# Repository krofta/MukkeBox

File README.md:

# MukkeBox_Electric

This is a project made with KiCAD.
During corona virus i was pretty bored at home and started to build my own portable bluetooth speaker and this is the result.
Additional I have to more repositories for software and mechanics:  
https://github.com/krofta/MukkeBox_Mechanic  
https://github.com/krofta/MukkeBox_Software

This PCB contains:  
Charger for 1-6s LiPo Packs (configured for 4s)  TI BQ24610  
ST microcontroller to controll the whole circuit STM32F030C6Tx  
Step up to make 4s pack-voltage to constant 24V TI TPS40210
Digital audio processor ST TDA7719 with i2c interface  
2x Class D audio amplifiers TI TPA3116D2  (in 2.1 sound system configuration with 20dB gain)

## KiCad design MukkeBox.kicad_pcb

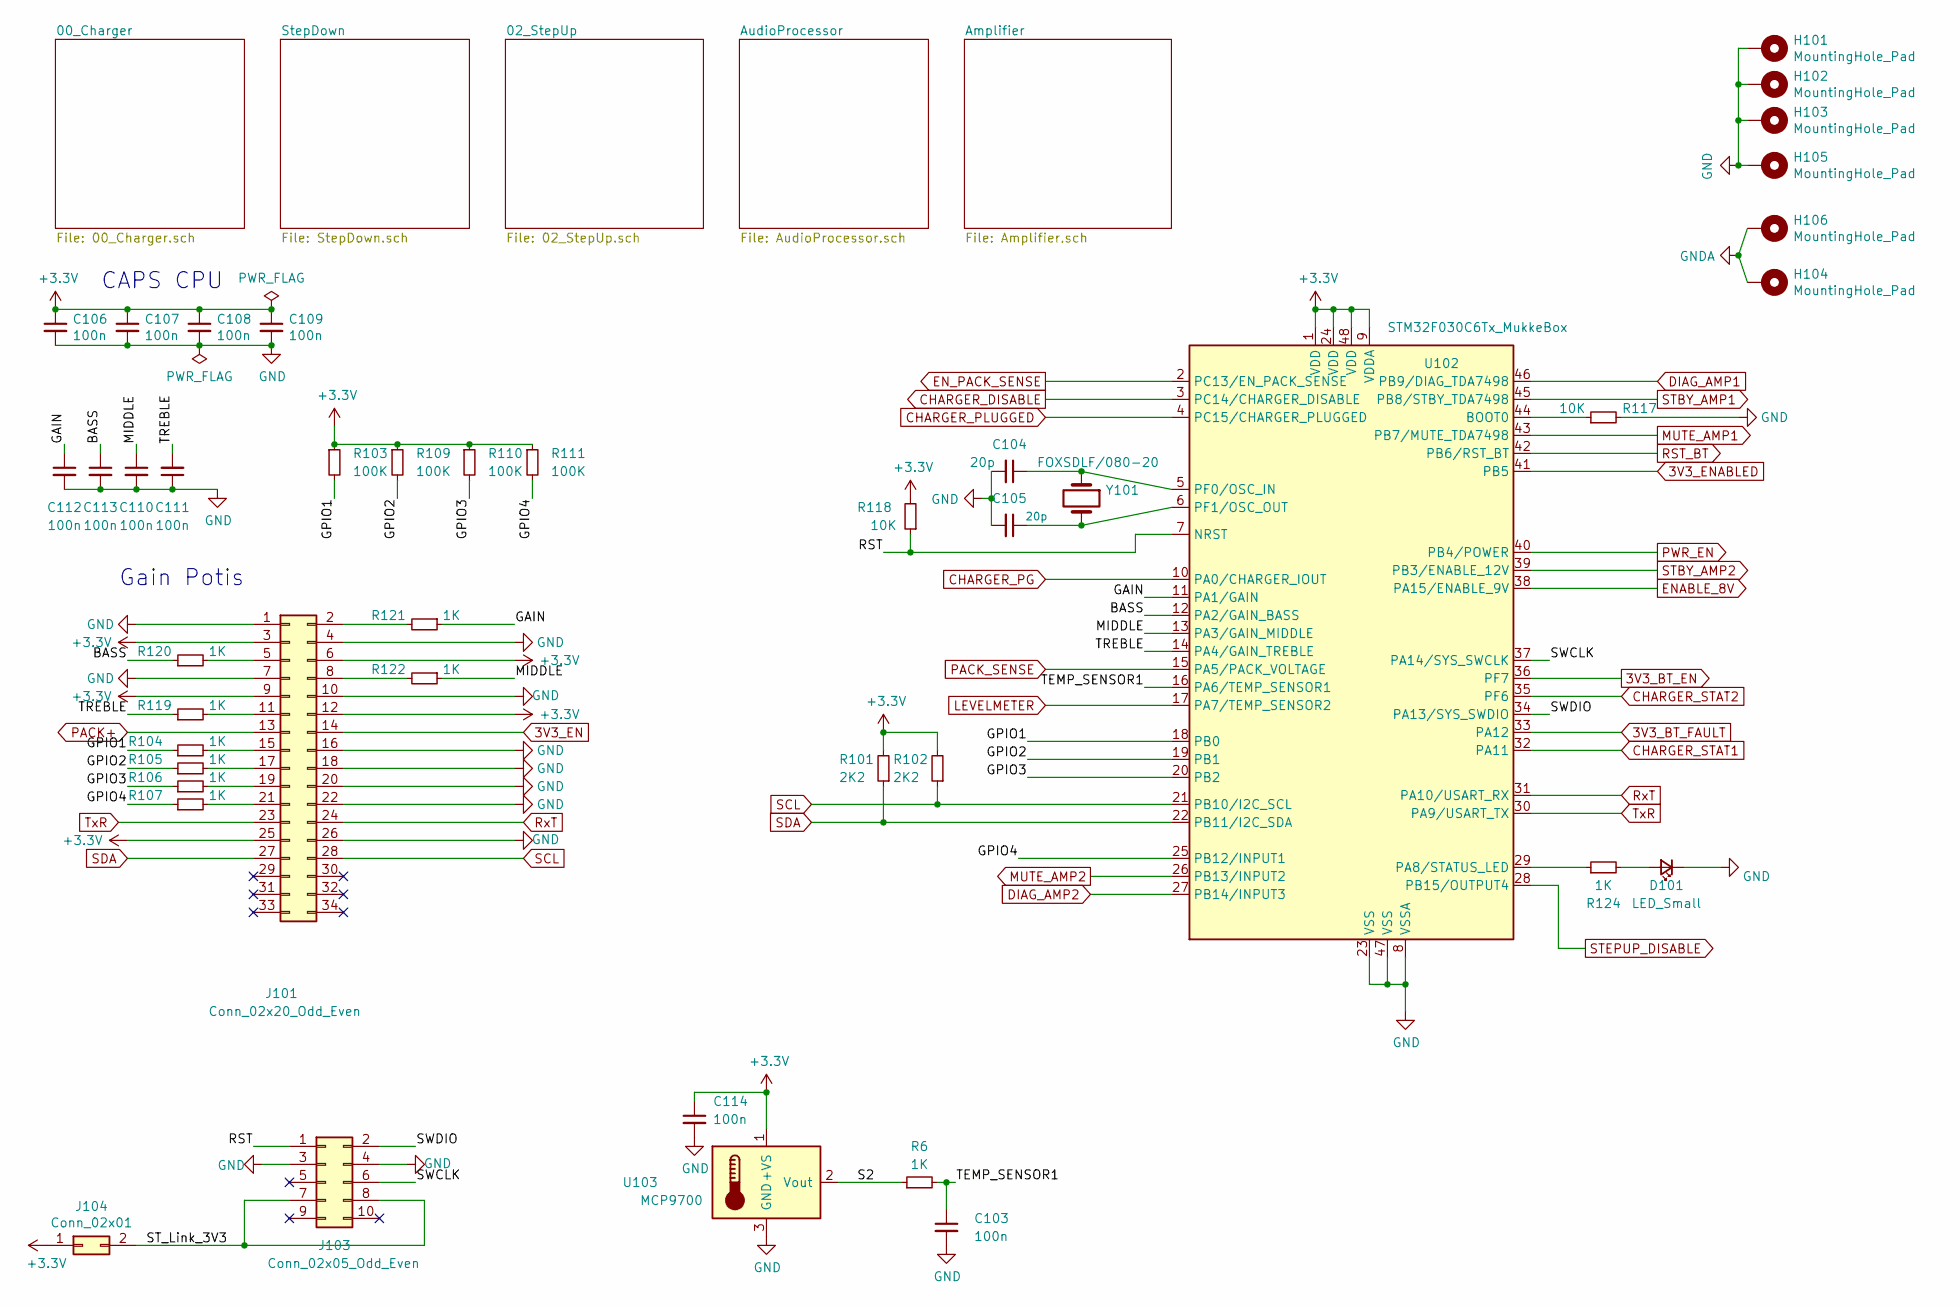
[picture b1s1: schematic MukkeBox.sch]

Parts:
C103, C106, C107, C108, C109, C110, C111, C112, C113, C114: 100n; C_0603_1608Metric_Pad1.05x0.95mm_HandSolder
C104, C105: 20p; C_0603_1608Metric_Pad1.05x0.95mm_HandSolder
D101: LED_Small; LED_D3.0mm
H101, H102, H103, H104, H105, H106: MountingHole_Pad; MountingHole_3.2mm_M3_DIN965_Pad
J101: Conn_02x20_Odd_Even; PinHeader_2x17_P2.54mm_Vertical
J103: Conn_02x05_Odd_Even; PinHeader_2x05_P2.54mm_Vertical
J104: Conn_02x01; PinHeader_1x02_P2.54mm_Vertical
R6, R104, R105, R106, R107, R119, R120, R121, R122, R124: 1K; R_0603_1608Metric_Pad1.05x0.95mm_HandSolder
R101, R102: 2K2; R_0603_1608Metric_Pad1.05x0.95mm_HandSolder
R103, R109, R110, R111: 100K; R_0603_1608Metric_Pad1.05x0.95mm_HandSolder
R117, R118: 10K; R_0603_1608Metric_Pad1.05x0.95mm_HandSolder
U102: STM32F030C6Tx_MukkeBox; LQFP-48_7x7mm_P0.5mm
U103: MCP9700; TO-92_Inline
Y101: FOXSDLF/080-20; Crystal_SMD_HC49-SD

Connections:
3V3_BT_EN: U102.36 (PF7); also elsewhere on the board
3V3_BT_FAULT: U102.33 (PA12); also elsewhere on the board
3V3_EN: J101.14; also elsewhere on the board
3V3_ENABLED: U102.41 (PB5); also elsewhere on the board
/BASS: C113.1, R120.1, U102.12 (PA2/GAIN_BASS)
/GAIN: C112.1, R121.1, U102.11 (PA1/GAIN)
/GPIO1: R103.2, R104.1, U102.18 (PB0)
/GPIO2: R105.1, R109.2, U102.19 (PB1)
/GPIO3: R106.1, R110.2, U102.20 (PB2)
/GPIO4: R107.1, R111.2, U102.25 (PB12/INPUT1)
/MIDDLE: C110.1, R122.1, U102.13 (PA3/GAIN_MIDDLE)
/RST: J103.1, R118.1, U102.7 (NRST)
/S2: R6.1, U103.2 (Vout)
/ST_Link_3V3: J103.7, J103.8, J104.2
/SWCLK: J103.6, U102.37 (PA14/SYS_SWCLK)
/SWDIO: J103.2, U102.34 (PA13/SYS_SWDIO)
/TEMP_SENSOR1: C103.1, R6.2, U102.16 (PA6/TEMP_SENSOR1)
/TREBLE: C111.2, R119.1, U102.14 (PA4/GAIN_TREBLE)
CHARGER_DISABLE: U102.3 (PC14/CHARGER_DISABLE); also elsewhere on the board
CHARGER_PG: U102.10 (PA0/CHARGER_IOUT); also elsewhere on the board
CHARGER_PLUGGED: U102.4 (PC15/CHARGER_PLUGGED); also elsewhere on the board
CHARGER_STAT1: U102.32 (PA11); also elsewhere on the board
CHARGER_STAT2: U102.35 (PF6); also elsewhere on the board
DIAG_AMP1: U102.46 (PB9/DIAG_TDA7498); also elsewhere on the board
DIAG_AMP2: U102.27 (PB14/INPUT3); also elsewhere on the board
ENABLE_8V: U102.38 (PA15/ENABLE_9V); also elsewhere on the board
EN_PACK_SENSE: U102.2 (PC13/EN_PACK_SENSE); also elsewhere on the board
GND: C103.2, C104.2, C105.2, C106.2, C107.2, C108.2, C109.2, C110.2, C111.1, C112.2, C113.2, C114.2, D101.1 (K), H101.1, H102.1, H103.1, H105.1, J101.1, J101.4, J101.7, J101.10, J101.16, J101.18, J101.20, J101.22, J101.26, J103.3, J103.4, R117.2, U102.8 (VSSA), U102.23 (VSS), U102.47 (VSS), U103.3 (GND); also elsewhere on the board
GNDA: H104.1, H106.1; also elsewhere on the board
LEVELMETER: U102.17 (PA7/TEMP_SENSOR2); also elsewhere on the board
MUTE_AMP1: U102.43 (PB7/MUTE_TDA7498); also elsewhere on the board
MUTE_AMP2: U102.26 (PB13/INPUT2); also elsewhere on the board
unnamed: C104.1, U102.5 (PF0/OSC_IN), Y101.1
unnamed: C105.1, U102.6 (PF1/OSC_OUT), Y101.2
unnamed: D101.2 (A), R124.2
unnamed: J101.2, R121.2
unnamed: J101.5, R120.2
unnamed: J101.8, R122.2
unnamed: J101.11, R119.2
unnamed: J101.15, R104.2
unnamed: J101.17, R105.2
unnamed: J101.19, R106.2
unnamed: J101.21, R107.2
unnamed: R117.1, U102.44 (BOOT0)
unnamed: R124.1, U102.29 (PA8/STATUS_LED)
PACK+: J101.13; also elsewhere on the board
PACK_SENSE: U102.15 (PA5/PACK_VOLTAGE); also elsewhere on the board
PWR_EN: U102.40 (PB4/POWER); also elsewhere on the board
RST_BT: U102.42 (PB6/RST_BT); also elsewhere on the board
RxT: J101.24, U102.31 (PA10/USART_RX); also elsewhere on the board
SCL: J101.28, R102.1, U102.21 (PB10/I2C_SCL); also elsewhere on the board
SDA: J101.27, R101.1, U102.22 (PB11/I2C_SDA); also elsewhere on the board
STBY_AMP1: U102.45 (PB8/STBY_TDA7498); also elsewhere on the board
STBY_AMP2: U102.39 (PB3/ENABLE_12V); also elsewhere on the board
STEPUP_DISABLE: U102.28 (PB15/OUTPUT4); also elsewhere on the board
TxR: J101.23, U102.30 (PA9/USART_TX); also elsewhere on the board

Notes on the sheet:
Gain Potis
CAPS CPU

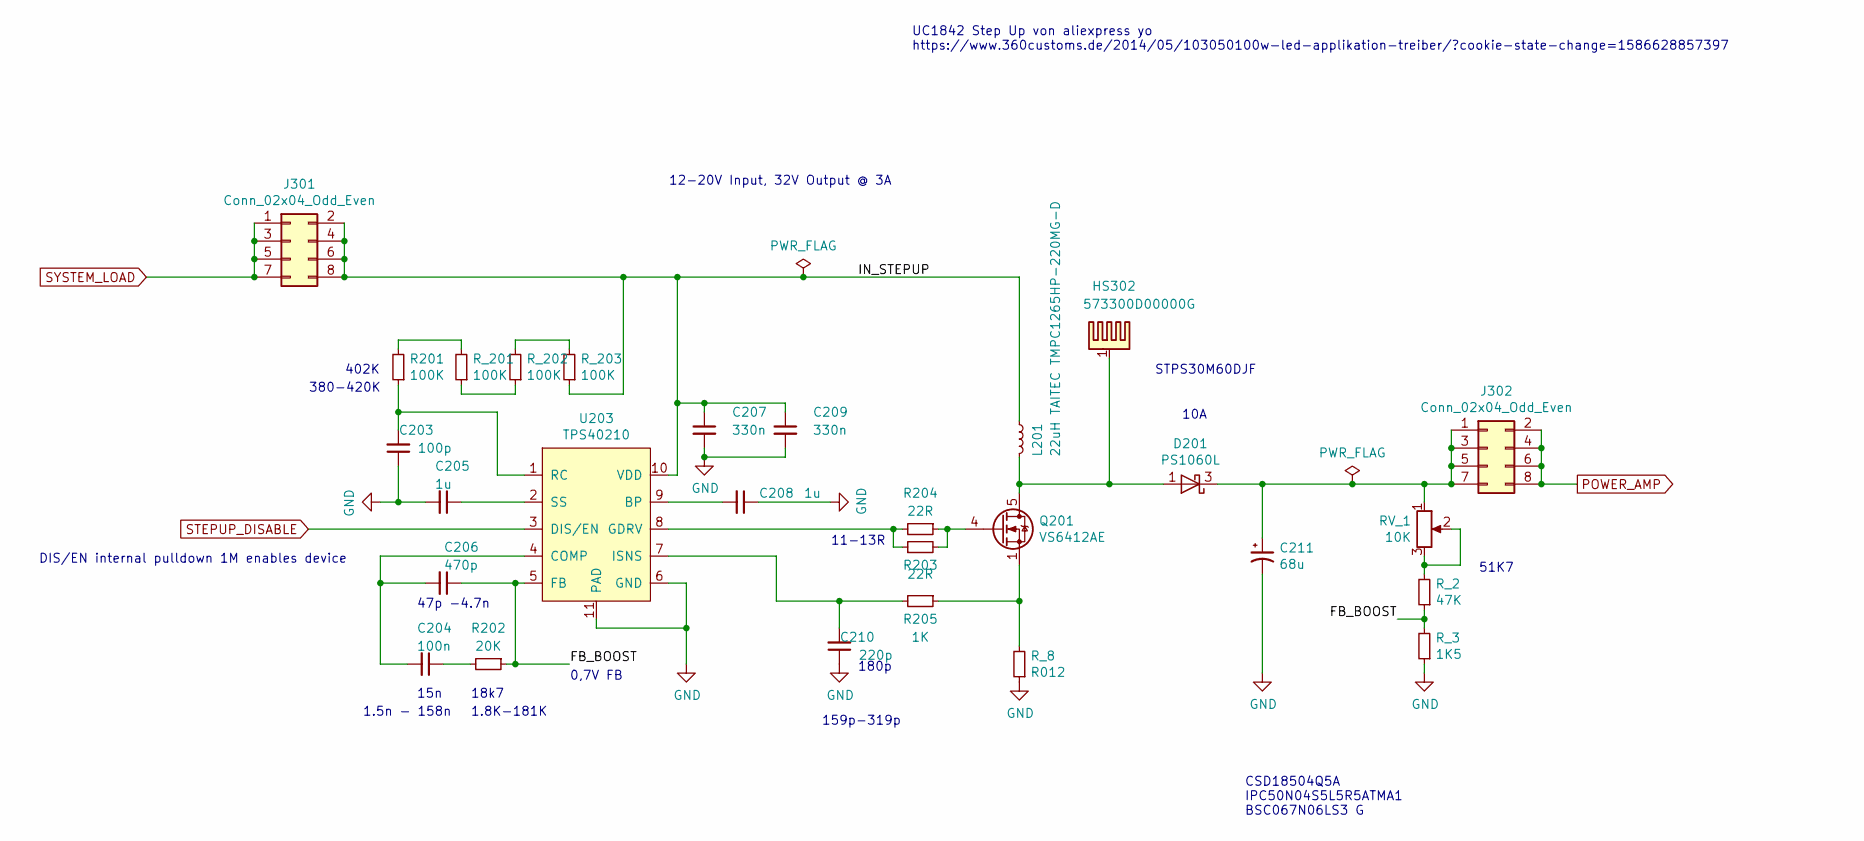
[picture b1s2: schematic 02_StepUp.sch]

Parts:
C203: 100p; C_0603_1608Metric_Pad1.05x0.95mm_HandSolder
C204: 100n; C_0603_1608Metric_Pad1.05x0.95mm_HandSolder
C205, C208: 1u; C_0603_1608Metric_Pad1.05x0.95mm_HandSolder
C206: 470p; C_0603_1608Metric_Pad1.05x0.95mm_HandSolder
C207, C209: 330n; C_1206_3216Metric
C210: 220p; C_0603_1608Metric_Pad1.05x0.95mm_HandSolder
C211: 68u; CP_Radial_D5.0mm_P2.50mm
D201: PS1060L; TO-277B
HS302: 573300D00000G; Heatsink_AAVID_573300D00010G_TO-263
J301, J302: Conn_02x04_Odd_Even; PinHeader_2x04_P2.54mm_Vertical
L201: 22uH TAITEC TMPC1265HP-220MG-D; TAITEC TMPC1265HP-220MG-D
Q201: VS6412AE; Diodes_PowerDI3333-8
R201: 100K; R_0603_1608Metric_Pad1.05x0.95mm_HandSolder
R202: 20K; R_0603_1608Metric_Pad1.05x0.95mm_HandSolder
R203, R204: 22R; R_0603_1608Metric_Pad1.05x0.95mm_HandSolder
R205: 1K; R_0603_1608Metric_Pad1.05x0.95mm_HandSolder
RV_1: 10K; Potentiometer_P250
R_2: 47K; R_0603_1608Metric_Pad1.05x0.95mm_HandSolder
R_3: 1K5; R_0603_1608Metric_Pad1.05x0.95mm_HandSolder
R_8: R012; R_2512_6332Metric_Pad1.52x3.35mm_HandSolder
R_201, R_202, R_203: 100K; R_0603_1608Metric_Pad1.05x0.95mm_HandSolder
U203: TPS40210; MSOP-10-1EP_3x3mm_P0.5mm_EP1.68x1.88mm

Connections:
/02_StepUp/FB_BOOST: C206.1, R202.1, R_2.1, R_3.2, U203.5 (FB); also elsewhere on the board
/02_StepUp/IN_STEPUP: C207.1, C209.1, J301.2, J301.4, J301.6, J301.8, L201.1, R_203.1, U203.10 (VDD); also elsewhere on the board
GND: C203.1, C205.2, C207.2, C208.1, C209.2, C210.1, C211.2, R_3.1, R_8.1, U203.6 (GND), U203.11 (PAD); also elsewhere on the board
unnamed: C203.2, R201.1, U203.1 (RC)
unnamed: C204.1, R202.2
unnamed: C204.2, C206.2, U203.4 (COMP)
unnamed: C205.1, U203.2 (SS)
unnamed: C208.2, U203.9 (BP)
unnamed: C210.2, R205.2, U203.7 (ISNS)
unnamed: C211.1, D201.3 (K), J302.1, J302.3, J302.5, J302.7, RV_1.1
unnamed: D201.1 (A), D201.2 (A), HS302.1, L201.2, Q201.5 (D)
unnamed 147: Q201.1 (S), Q201.2 (S), Q201.3 (S), R205.1, R_8.2; also elsewhere on the board
unnamed: Q201.4 (G), R203.2, R204.1
unnamed 167: R201.2, R_201.2; also elsewhere on the board
unnamed: R203.1, R204.2, U203.8 (GDRV)
unnamed 169: RV_1.2, RV_1.3, R_2.2; also elsewhere on the board
unnamed: R_201.1, R_202.1
unnamed: R_202.2, R_203.2
POWER_AMP: J302.2, J302.4, J302.6, J302.8; also elsewhere on the board
STEPUP_DISABLE: U203.3 (DIS/EN); also elsewhere on the board
SYSTEM_LOAD: J301.1, J301.3, J301.5, J301.7; also elsewhere on the board

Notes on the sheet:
UC1842 Step Up von aliexpress yo https://www.360customs.de/2014/05/103050100w-led-applikation-treiber/?cookie-state-change=1586628857397
DIS/EN internal pulldown 1M enables device
12-20V Input, 32V Output @ 3A
51K7
18k7
15n
402K
180p
10A
47p -4.7n
1.5n - 158n
1.8K-181K
159p-319p
11-13R
380-420K
CSD18504Q5A IPC50N04S5L5R5ATMA1 BSC067N06LS3 G
STPS30M60DJF
0,7V FB

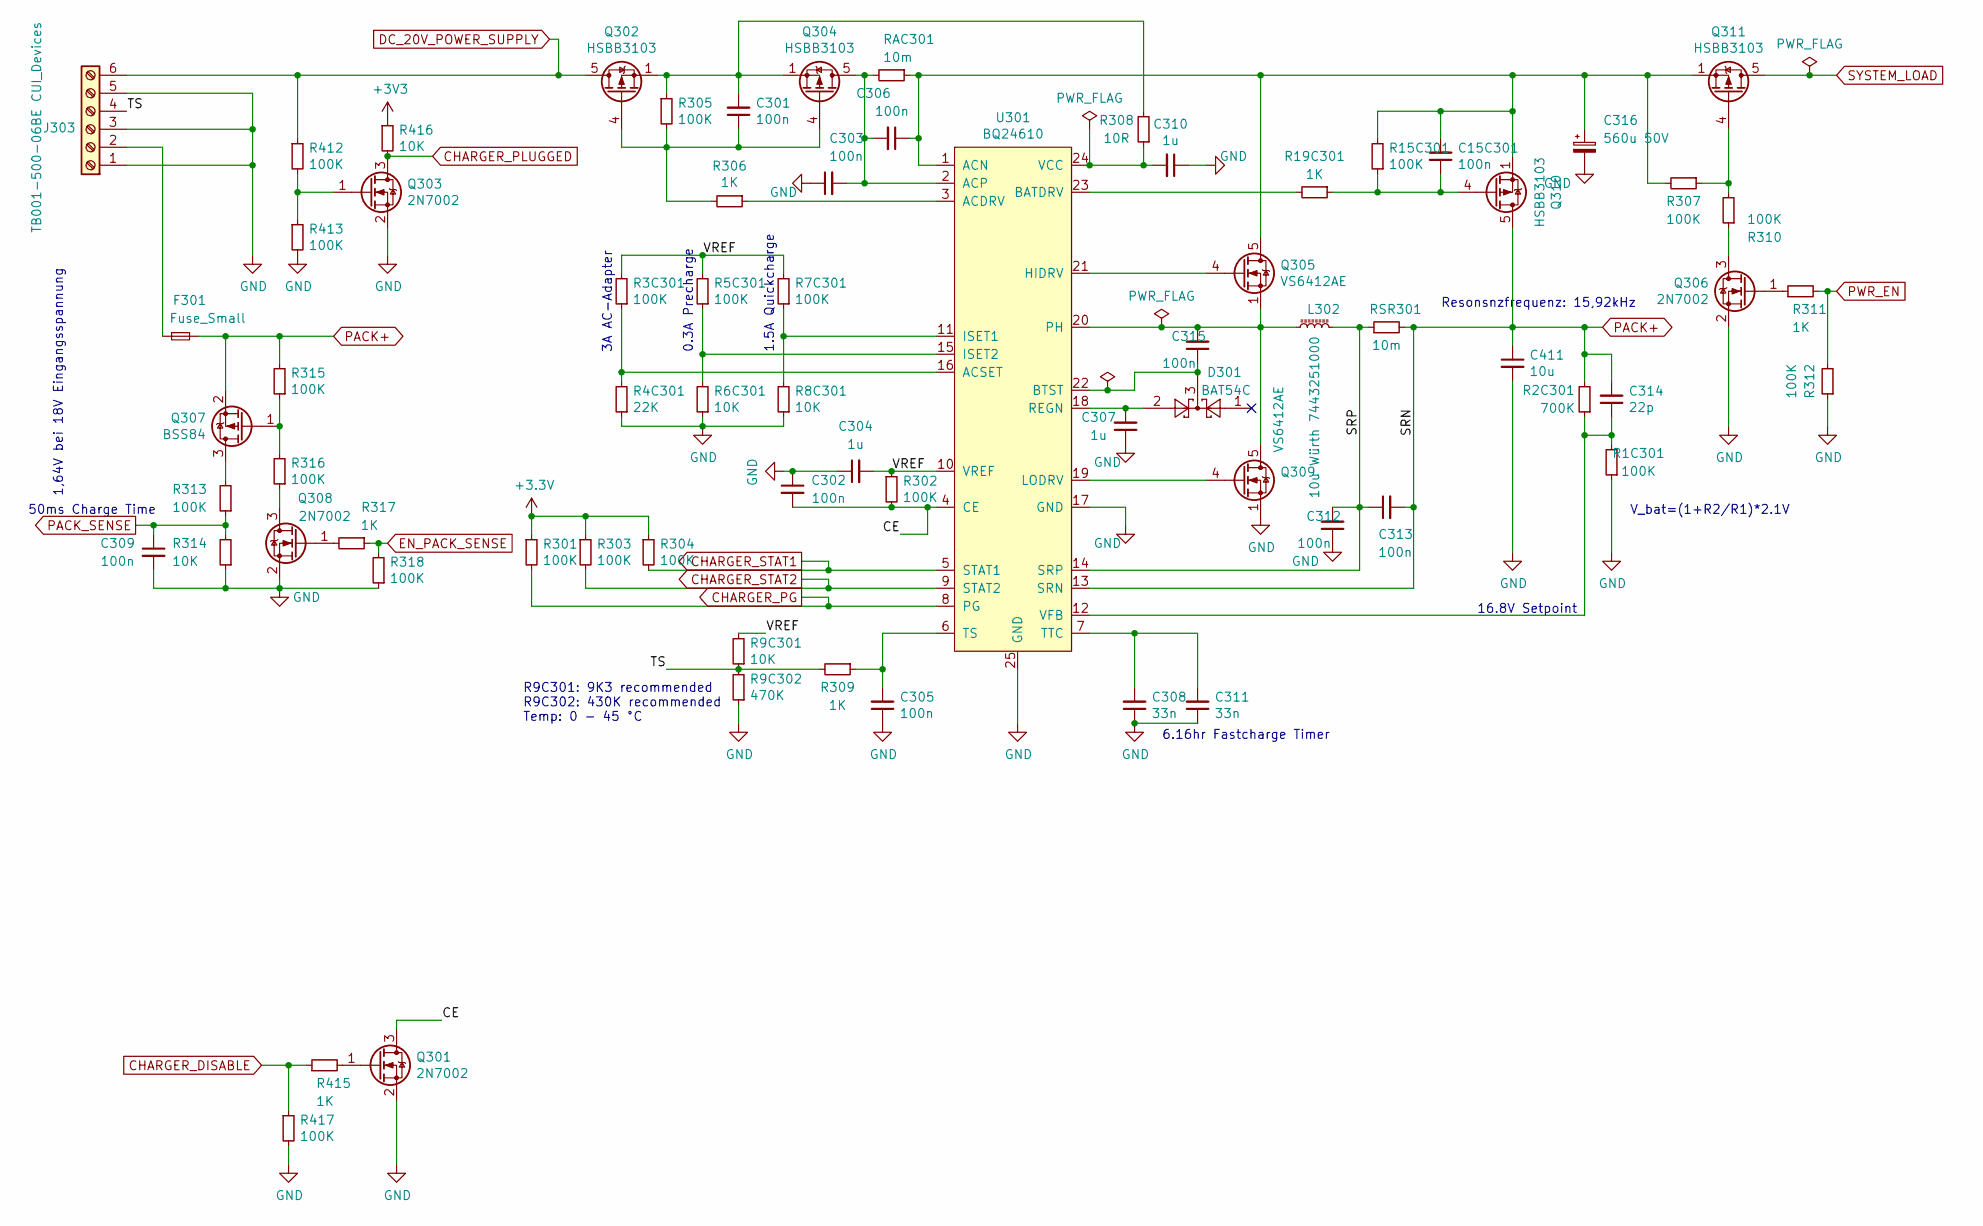
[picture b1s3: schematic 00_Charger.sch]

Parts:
C15C301, C301, C302, C303, C305, C306, C309, C312, C313, C315: 100n; C_0603_1608Metric_Pad1.05x0.95mm_HandSolder
C304, C307, C310: 1u; C_1210_3225Metric
C308, C311: 33n; C_0603_1608Metric_Pad1.05x0.95mm_HandSolder
C314: 22p; C_0603_1608Metric_Pad1.05x0.95mm_HandSolder
C316: 560u 50V; CP_Radial_D12.5mm_P5.00mm
C411: 10u; C_1206_3216Metric_Pad1.42x1.75mm_HandSolder
D301: BAT54C; SOT-23
F301: Fuse_Small; Fuseholder_Cylinder-5x20mm_Schurter_0031_8201_Horizontal_Op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
J303: TB001-500-06BE CUI_Devices; TerminalBlock_RND_205-00049_1x06_P5.00mm_Horizontal
L302: 10u Würth 7443251000; L_Wuerth_HCI-1050
Q301, Q303, Q306, Q308: 2N7002; SOT-23
Q302, Q304, Q310, Q311: HSBB3103; Diodes_PowerDI3333-8
Q305, Q309: VS6412AE; Diodes_PowerDI3333-8
Q307: BSS84; SOT-23
R1C301, R3C301, R5C301, R7C301, R15C301, R301, R302, R303, R304, R305, R307, R310, R312, R313, R315, R316, R318, R412, R413, R417: 100K; R_0603_1608Metric_Pad1.05x0.95mm_HandSolder
R2C301: 700K; R_0603_1608Metric_Pad1.05x0.95mm_HandSolder
R4C301: 22K; R_0603_1608Metric_Pad1.05x0.95mm_HandSolder
R6C301, R8C301, R9C301, R314, R416: 10K; R_0603_1608Metric_Pad1.05x0.95mm_HandSolder
R9C302: 470K; R_0603_1608Metric_Pad1.05x0.95mm_HandSolder
R19C301, R306, R309, R311, R317, R415: 1K; R_0603_1608Metric_Pad1.05x0.95mm_HandSolder
R308: 10R; R_0603_1608Metric_Pad1.05x0.95mm_HandSolder
RAC301: 10m; R_1206_3216Metric_Pad1.42x1.75mm_HandSolder
RSR301: 10m; R_1206_3216Metric_Pad1.42x1.75mm_HandSolder
U301: BQ24610; VQFN-24-1EP_4x4mm_P0.5mm_EP2.45x2.45mm_ThermalVias

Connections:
/00_Charger/CE: C302.2, Q301.3 (D), R302.2, U301.4 (CE)
/00_Charger/SRP: C312.2, C313.1, L302.2, RSR301.1, U301.14 (SRP); also elsewhere on the board
/00_Charger/TS: J303.4, R9C301.1, R9C302.2, R309.2; also elsewhere on the board
/00_Charger/VREF: C304.2, R3C301.2, R5C301.2, R7C301.2, R9C301.2, R302.1, U301.10 (VREF); also elsewhere on the board
CHARGER_DISABLE: R415.1, R417.1; also elsewhere on the board
CHARGER_PG: R301.2, U301.8 (PG); also elsewhere on the board
CHARGER_PLUGGED: Q303.3 (D), R416.2; also elsewhere on the board
CHARGER_STAT1: R304.2, U301.5 (STAT1); also elsewhere on the board
CHARGER_STAT2: R303.2, U301.9 (STAT2); also elsewhere on the board
DC_20V_POWER_SUPPLY: J303.6, Q302.5 (D), R412.1; also elsewhere on the board
EN_PACK_SENSE: R317.1, R318.2; also elsewhere on the board
GND: C302.1, C303.1, C304.1, C305.1, C307.1, C308.1, C309.2, C310.1, C311.1, C312.1, C316.2, C411.2, J303.1, J303.3, J303.5, Q301.2 (S), Q303.2 (S), Q306.2 (S), Q308.2 (S), Q309.1 (S), Q309.2 (S), Q309.3 (S), R1C301.1, R4C301.1, R6C301.1, R8C301.1, R9C302.1, R312.1, R314.1, R318.1, R413.2, R417.2, U301.17 (GND), U301.25 (GND); also elsewhere on the board
unnamed: C301.1, Q302.4 (G), Q304.4 (G), R305.2, R306.2
unnamed: C301.2, Q302.1 (S), Q302.2 (S), Q302.3 (S), Q304.1 (S), Q304.2 (S), Q304.3 (S), R305.1, R308.2
unnamed 86: C303.2, C306.2, Q304.5 (D), RAC301.2, U301.2 (ACP); also elsewhere on the board
unnamed: C305.2, R309.1, U301.6 (TS)
unnamed 88: C15C301.2, C306.1, C316.1, Q305.5 (D), Q310.1 (S), Q310.2 (S), Q310.3 (S), Q311.1 (S), Q311.2 (S), Q311.3 (S), R15C301.2, R307.2, RAC301.1, U301.1 (ACN); also elsewhere on the board
unnamed: C307.2, D301.2, U301.18 (REGN)
unnamed: C308.2, C311.2, U301.7 (TTC)
unnamed: C310.2, R308.1, U301.24 (VCC)
unnamed 92: C314.1, R1C301.2, R2C301.1, U301.12 (VFB); also elsewhere on the board
unnamed: C315.1, D301.3, U301.22 (BTST)
unnamed: C315.2, L302.1, Q305.1 (S), Q305.2 (S), Q305.3 (S), Q309.5 (D), U301.20 (PH)
unnamed 95: C15C301.1, Q310.4 (G), R15C301.1, R19C301.1; also elsewhere on the board
unnamed: F301.1, J303.2
unnamed: Q301.1 (G), R415.2
unnamed: Q303.1 (G), R412.2, R413.1
unnamed: Q305.4 (G), U301.21 (HIDRV)
unnamed: Q306.1 (G), R311.1
unnamed: Q306.3 (D), R310.1
unnamed: Q307.1 (G), R315.1, R316.2
unnamed: Q307.3 (D), R313.2
unnamed: Q308.1 (G), R317.2
unnamed: Q308.3 (D), R316.1
unnamed: Q309.4 (G), U301.19 (LODRV)
unnamed: Q311.4 (G), R307.1, R310.2
unnamed: R306.1, U301.3 (ACDRV)
unnamed 173: R3C301.1, R4C301.2, U301.16 (ACSET); also elsewhere on the board
unnamed 174: R5C301.1, R6C301.2, U301.15 (ISET2); also elsewhere on the board
unnamed 175: R7C301.1, R8C301.2, U301.11 (ISET1); also elsewhere on the board
unnamed 176: R19C301.2, U301.23 (BATDRV); also elsewhere on the board
PACK+: C313.2, C314.2, C411.1, F301.2, Q307.2 (S), Q310.5 (D), R2C301.2, R315.2, RSR301.2, U301.13 (SRN); also elsewhere on the board
PACK_SENSE: C309.1, R313.1, R314.2; also elsewhere on the board
PWR_EN: R311.2, R312.2; also elsewhere on the board
SYSTEM_LOAD: Q311.5 (D); also elsewhere on the board

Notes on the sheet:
1,64V bei 18V Eingangsspannung
V_bat=(1+R2/R1)*2.1V
3A AC-Adapter
0.3A Precharge
1.5A Quickcharge
16.8V Setpoint
6.16hr Fastcharge Timer
Resonsnzfrequenz: 15,92kHz
50ms Charge Time
R9C301: 9K3 recommended R9C302: 430K recommended Temp: 0 - 45 °C

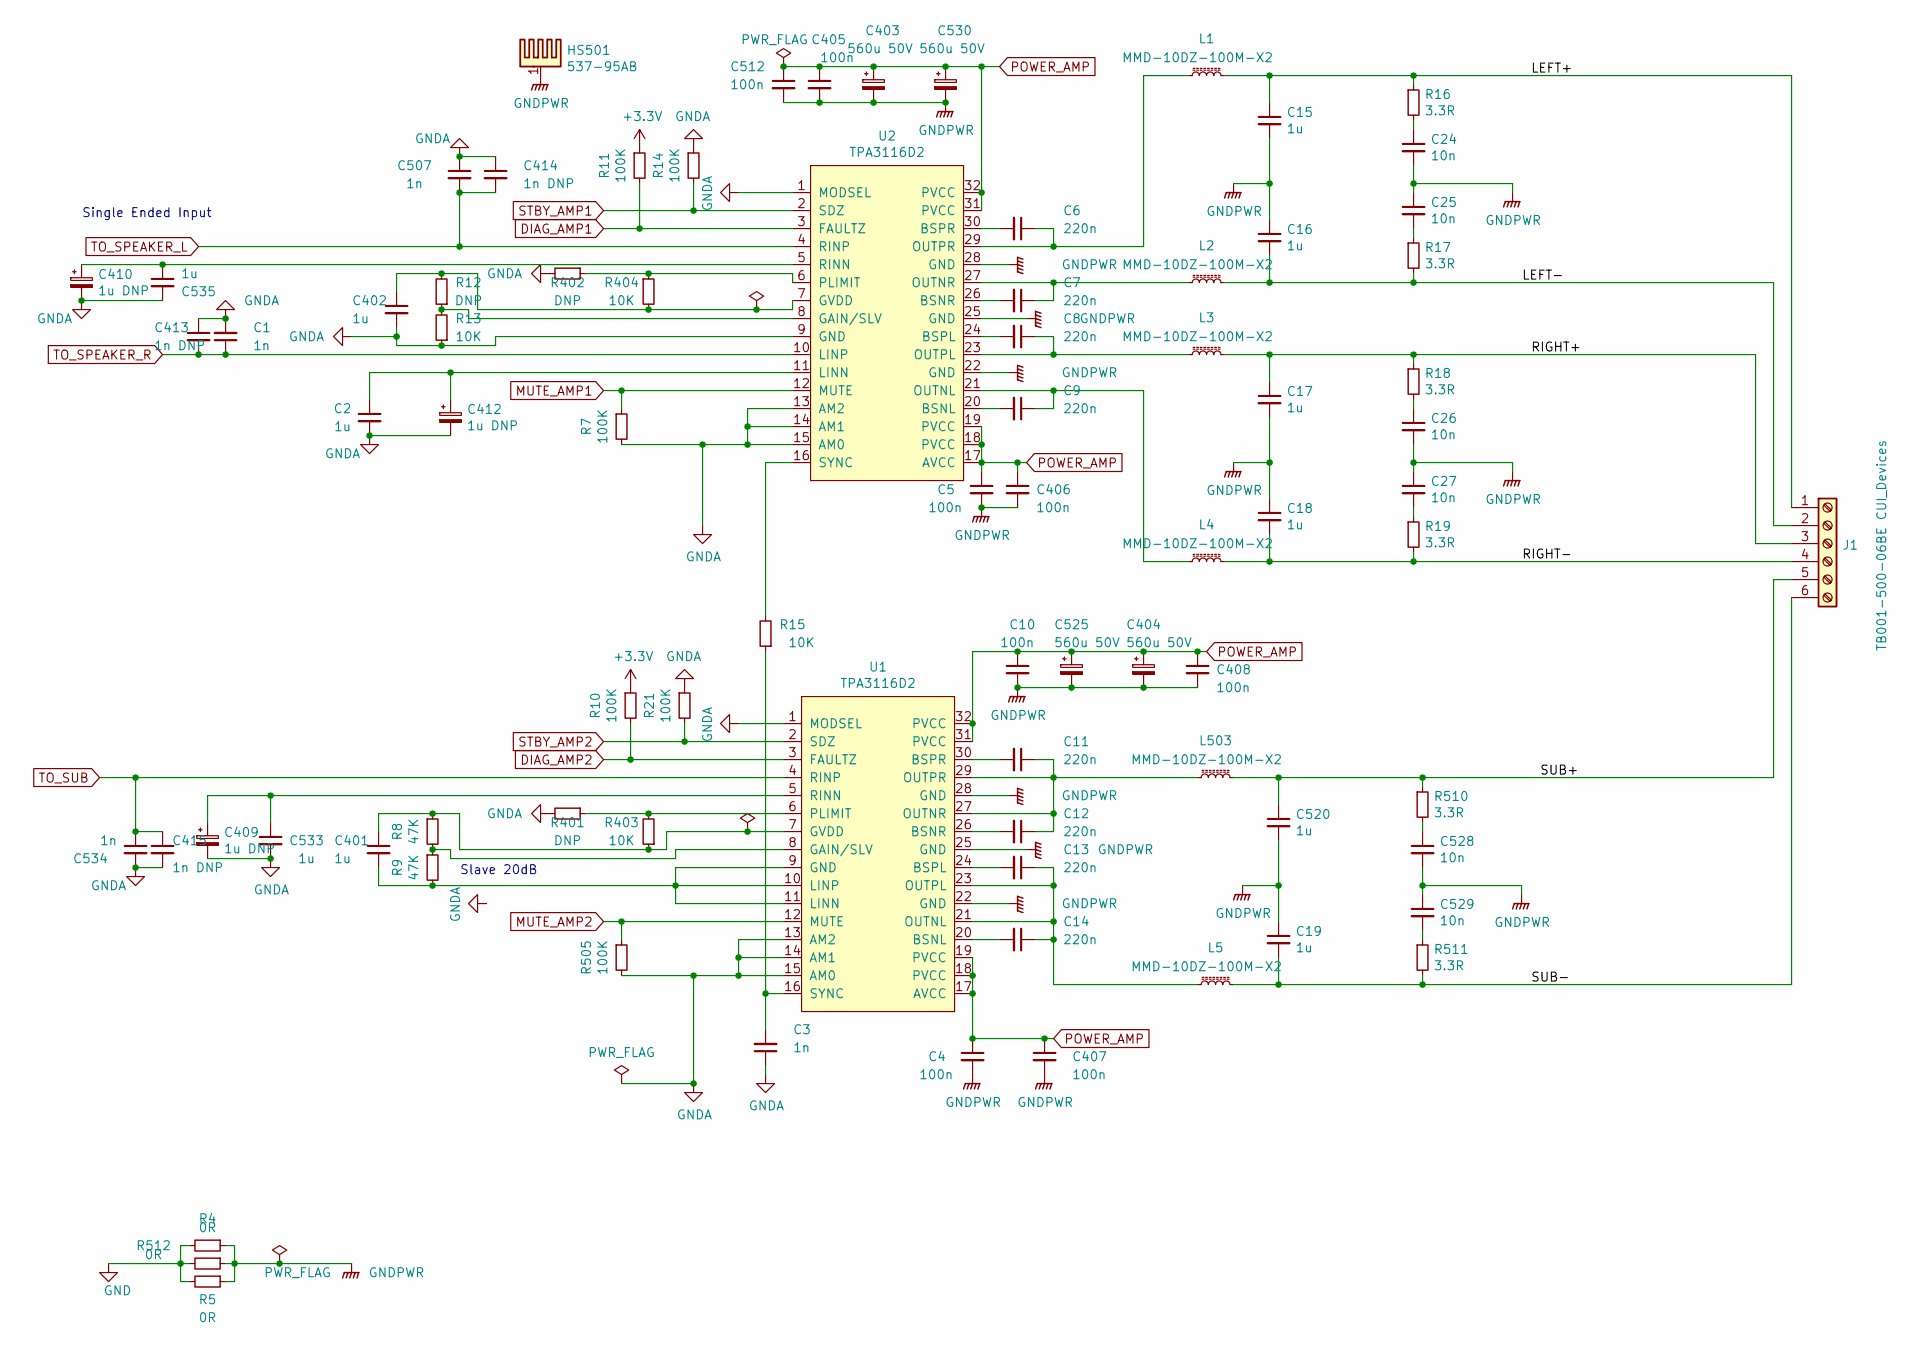
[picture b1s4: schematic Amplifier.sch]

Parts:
C1, C507, C534: 1n; C_Rect_L7.0mm_W2.5mm_P5.00mm
C2, C533, C535: 1u; C_Rect_L7.2mm_W3.5mm_P5.00mm_FKS2_FKP2_MKS2_MKP2
C3: 1n; C_0603_1608Metric_Pad1.05x0.95mm_HandSolder
C4, C5, C10, C405, C406, C407, C408, C512: 100n; C_0603_1608Metric_Pad1.05x0.95mm_HandSolder
C6, C7, C8, C9, C11, C12, C13, C14: 220n; C_0603_1608Metric_Pad1.05x0.95mm_HandSolder
C15, C16, C17, C18, C19, C520: 1u; C_1210_3225Metric_Pad1.42x2.65mm_HandSolder
C24, C25, C26, C27, C528, C529: 10n; C_1210_3225Metric_Pad1.42x2.65mm_HandSolder
C401, C402: 1u; C_0603_1608Metric_Pad1.05x0.95mm_HandSolder
C403, C404, C525, C530: 560u 50V; CP_Radial_D12.5mm_P5.00mm
C409, C410, C412: 1u DNP; CP_EIA-3216-18_Kemet-A
C413, C414, C415: 1n DNP; C_0603_1608Metric_Pad1.05x0.95mm_HandSolder
HS501: 537-95AB; Heatsink_57.9x36.8mm_4xFixation3.17mm_537-95AB
J1: TB001-500-06BE CUI_Devices; TerminalBlock_RND_205-00049_1x06_P5.00mm_Horizontal
L1, L2, L3, L4, L5, L503: MMD-10DZ-100M-X2; L_Wuerth_HCI-1030
R4, R5, R512: 0R; R_1206_3216Metric_Pad1.42x1.75mm_HandSolder
R7, R10, R11, R14, R21, R505: 100K; R_0603_1608Metric_Pad1.05x0.95mm_HandSolder
R8, R9: 47K; R_0603_1608Metric_Pad1.05x0.95mm_HandSolder
R12, R401, R402: DNP; R_0603_1608Metric_Pad1.05x0.95mm_HandSolder
R13, R15, R403, R404: 10K; R_0603_1608Metric_Pad1.05x0.95mm_HandSolder
R16, R17, R18, R19, R510, R511: 3.3R; R_1210_3225Metric_Pad1.42x2.65mm_HandSolder
U1, U2: TPA3116D2; HTSSOP-32-TPA3116D2

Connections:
/Amplifier/LEFT+: C15.1, J1.1, L1.2, R16.1
/Amplifier/LEFT-: C16.2, J1.2, L2.2, R17.2
/Amplifier/RIGHT+: C17.1, J1.3, L3.2, R18.1
/Amplifier/RIGHT-: C18.2, J1.4, L4.2, R19.2
/Amplifier/SUB+: C520.1, J1.5, L503.2, R510.1
/Amplifier/SUB-: C19.2, J1.6, L5.2, R511.2
DIAG_AMP1: R11.2, U2.3 (FAULTZ); also elsewhere on the board
DIAG_AMP2: R10.2, U1.3 (FAULTZ); also elsewhere on the board
GND: R4.2, R5.2, R512.2; also elsewhere on the board
GNDA: C1.2, C2.2, C3.1, C402.2, C409.2, C410.2, C412.2, C413.1, C414.1, C415.2, C507.1, C533.2, C534.2, C535.2, R7.2, R13.1, R14.1, R21.1, R401.2, R402.2, R505.2, U1.1 (MODSEL), U1.13 (AM2), U1.14 (AM1), U1.15 (AM0), U2.1 (MODSEL), U2.9 (GND), U2.13 (AM2), U2.14 (AM1), U2.15 (AM0); also elsewhere on the board
GNDPWR: C4.2, C5.2, C10.2, C15.2, C16.1, C17.2, C18.1, C19.1, C24.2, C25.1, C26.2, C27.1, C403.2, C404.2, C405.2, C406.2, C407.2, C408.2, C512.2, C520.2, C525.2, C528.2, C529.1, C530.2, HS501.1, R4.1, R5.1, R512.1, U1.22 (GND), U1.25 (GND), U1.28 (GND), U2.22 (GND), U2.25 (GND), U2.28 (GND)
MUTE_AMP1: R7.1, U2.12 (MUTE); also elsewhere on the board
MUTE_AMP2: R505.1, U1.12 (MUTE); also elsewhere on the board
unnamed: C2.1, C412.1, U2.11 (LINN)
unnamed: C3.2, R15.1, U1.16 (SYNC)
unnamed: C6.1, L1.1, U2.29 (OUTPR)
unnamed: C6.2, U2.30 (BSPR)
unnamed: C7.1, L2.1, U2.27 (OUTNR)
unnamed: C7.2, U2.26 (BSNR)
unnamed: C8.1, L3.1, U2.23 (OUTPL)
unnamed: C8.2, U2.24 (BSPL)
unnamed: C9.1, L4.1, U2.21 (OUTNL)
unnamed: C9.2, U2.20 (BSNL)
unnamed: C11.1, C12.1, L503.1, U1.27 (OUTNR), U1.29 (OUTPR)
unnamed: C11.2, U1.30 (BSPR)
unnamed: C12.2, U1.26 (BSNR)
unnamed: C13.1, C14.1, L5.1, U1.21 (OUTNL), U1.23 (OUTPL)
unnamed: C13.2, U1.24 (BSPL)
unnamed: C14.2, U1.20 (BSNL)
unnamed: C24.1, R16.2
unnamed: C25.2, R17.1
unnamed: C26.1, R18.2
unnamed: C27.2, R19.1
unnamed: C401.1, R8.1, R403.1, U1.7 (GVDD)
unnamed: C401.2, R9.2, U1.9 (GND), U1.10 (LINP), U1.11 (LINN)
unnamed: C402.1, R12.2, R404.2, U2.7 (GVDD)
unnamed: C409.1, C533.1, U1.5 (RINN)
unnamed: C410.1, C535.1, U2.5 (RINN)
unnamed: C528.1, R510.2
unnamed: C529.2, R511.1
unnamed: R8.2, R9.1, U1.8 (GAIN/SLV)
unnamed: R12.1, R13.2, U2.8 (GAIN/SLV)
unnamed: R15.2, U2.16 (SYNC)
unnamed: R401.1, R403.2, U1.6 (PLIMIT)
unnamed: R402.1, R404.1, U2.6 (PLIMIT)
POWER_AMP: C4.1, C5.1, C10.1, C403.1, C404.1, C405.1, C406.1, C407.1, C408.1, C512.1, C525.1, C530.1, U1.17 (AVCC), U1.18 (PVCC), U1.19 (PVCC), U1.31 (PVCC), U1.32 (PVCC), U2.17 (AVCC), U2.18 (PVCC), U2.19 (PVCC), U2.31 (PVCC), U2.32 (PVCC); also elsewhere on the board
STBY_AMP1: R14.2, U2.2 (SDZ); also elsewhere on the board
STBY_AMP2: R21.2, U1.2 (SDZ); also elsewhere on the board
TO_SPEAKER_L: C414.2, C507.2, U2.4 (RINP); also elsewhere on the board
TO_SPEAKER_R: C1.1, C413.2, U2.10 (LINP); also elsewhere on the board
TO_SUB: C415.1, C534.1, U1.4 (RINP); also elsewhere on the board

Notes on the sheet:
Single Ended Input
Slave 20dB
